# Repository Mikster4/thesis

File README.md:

# Thesis

Repo containing all files, design and photos created for the master thesis

# Links

Inverse kinematics: https://www.xarg.org/paper/inverse-kinematics-of-a-stewart-platform/

Simulation af en platform (i JS??): https://github.com/infusion/Stewart

Bibliotek til platform med servoer: https://github.com/Yeok-c/Stewart_Py

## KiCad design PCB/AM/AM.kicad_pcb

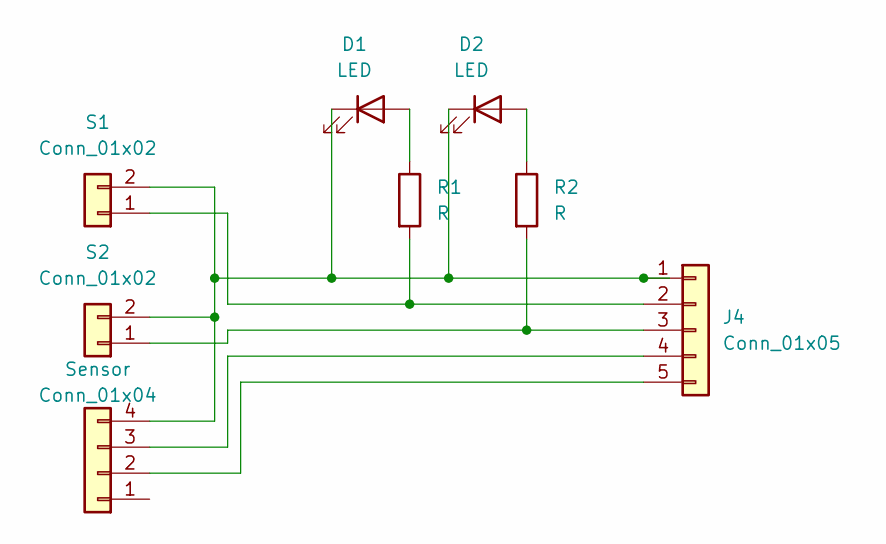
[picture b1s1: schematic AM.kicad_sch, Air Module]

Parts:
D1, D2: LED; LED_D5.0mm
J4: Conn_01x05; PinHeader_1x05_P2.54mm_Vertical
R1, R2: R; R_Axial_DIN0204_L3.6mm_D1.6mm_P7.62mm_Horizontal
S1, S2: Conn_01x02; PinHeader_1x02_P2.54mm_Vertical
Sensor: Conn_01x04; PinHeader_1x04_P2.54mm_Vertical

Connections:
unnamed: D1.1 (K), D2.1 (K), J4.1, S1.2, S2.2, Sensor.4
unnamed: D1.2 (A), R1.1
unnamed: D2.2 (A), R2.1
unnamed: J4.2, R1.2, S1.1
unnamed: J4.3, R2.2, S2.1
unnamed: J4.5, Sensor.2
unnamed: J4.4, Sensor.3

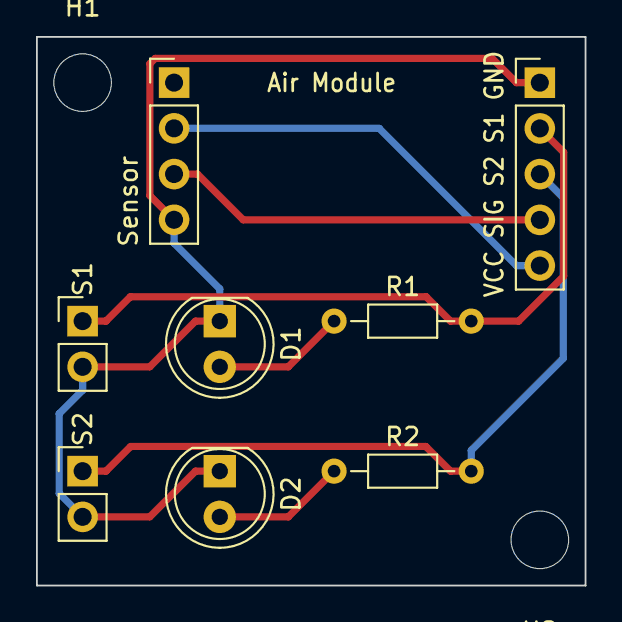
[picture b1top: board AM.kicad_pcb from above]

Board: 2 copper layers, 30.5 x 30.5 mm, 10 parts (0 on the bottom side), 7 nets.

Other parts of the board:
H1, H2: MountingHole_3.2mm_M3

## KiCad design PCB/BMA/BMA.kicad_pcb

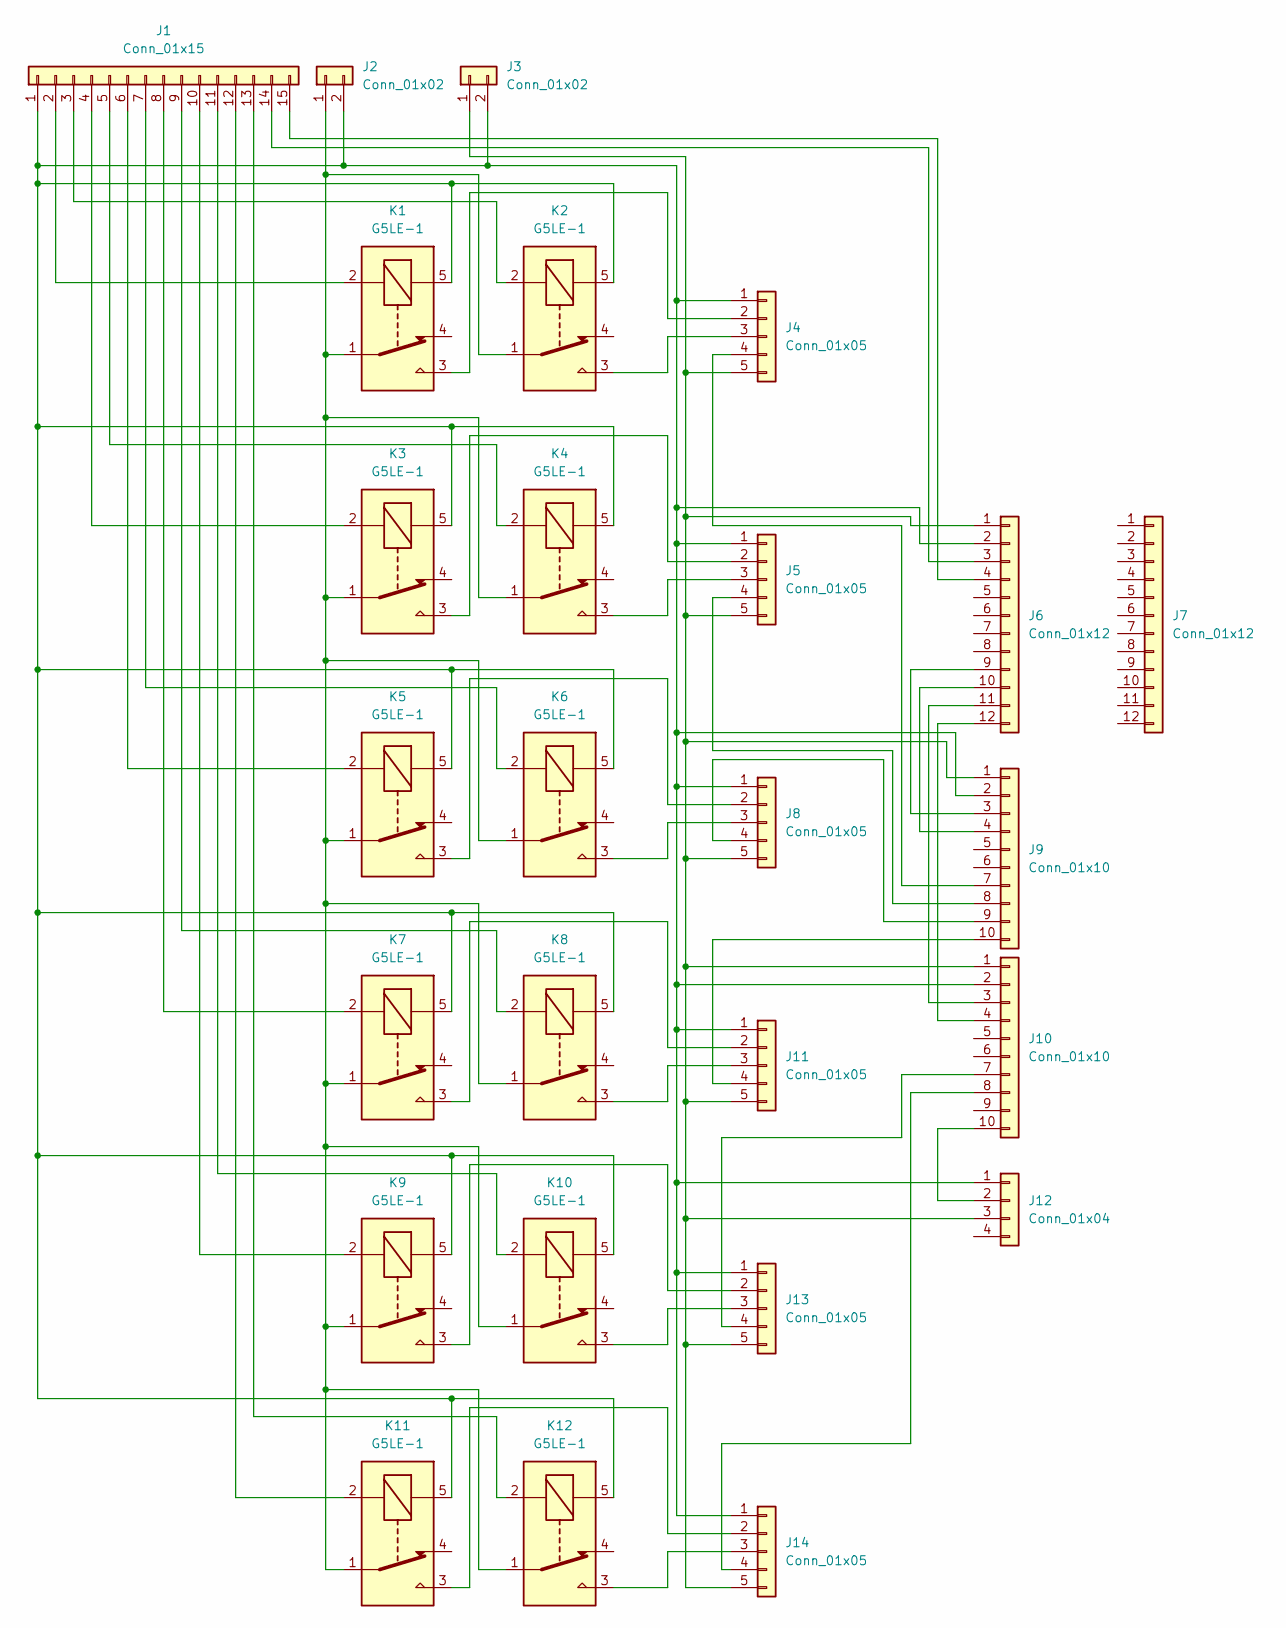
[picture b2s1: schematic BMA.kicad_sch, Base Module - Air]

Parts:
J1: Conn_01x15; PinHeader_1x15_P2.54mm_Vertical
J2, J3: Conn_01x02; PinHeader_1x02_P2.54mm_Vertical
J4, J5, J8, J11, J13, J14: Conn_01x05; PinHeader_1x05_P2.54mm_Vertical
J6, J7: Conn_01x12; PinHeader_1x12_P2.54mm_Vertical
J9, J10: Conn_01x10; PinHeader_1x10_P2.54mm_Vertical
J12: Conn_01x04; PinHeader_1x04_P2.54mm_Vertical
K1, K2, K3, K4, K5, K6, K7, K8, K9, K10, K11, K12: G5LE-1; Relay_SPDT_Omron-G5LE-1

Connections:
unnamed: J1.1, J2.2, J3.2, J4.1, J5.1, J6.2, J8.1, J9.2, J10.2, J11.1, J12.1, J13.1, J14.1, K1.5, K2.5, K3.5, K4.5, K5.5, K6.5, K7.5, K8.5, K9.5, K10.5, K11.5, K12.5
unnamed: J1.2, K1.2
unnamed: J1.3, K2.2
unnamed: J1.4, K3.2
unnamed: J1.5, K4.2
unnamed: J1.6, K5.2
unnamed: J1.7, K6.2
unnamed: J1.8, K7.2
unnamed: J1.9, K8.2
unnamed: J1.10, K9.2
unnamed: J1.11, K10.2
unnamed: J1.12, K11.2
unnamed: J1.13, K12.2
unnamed: J1.14, J6.3
unnamed: J1.15, J6.4
unnamed: J2.1, K1.1, K2.1, K3.1, K4.1, K5.1, K6.1, K7.1, K8.1, K9.1, K10.1, K11.1, K12.1
unnamed: J4.2, K1.3
unnamed: J4.3, K2.3
unnamed: J4.4, J9.7
unnamed: J5.2, K3.3
unnamed: J5.3, K4.3
unnamed: J5.4, J9.8
unnamed: J6.9, J9.3
unnamed: J6.10, J9.4
unnamed: J8.2, K5.3
unnamed: J8.3, K6.3
unnamed: J8.4, J9.9
unnamed: J3.1, J4.5, J5.5, J6.1, J8.5, J9.1, J10.1, J11.5, J12.3, J13.5, J14.5
unnamed: J6.11, J10.3
unnamed: J6.12, J10.4
unnamed: J10.7, J13.4
unnamed: J10.8, J14.4
unnamed: J10.10, J12.2
unnamed: J11.2, K7.3
unnamed: J11.3, K8.3
unnamed: J9.10, J11.4
unnamed: J13.2, K9.3
unnamed: J13.3, K10.3
unnamed: J14.2, K11.3
unnamed: J14.3, K12.3

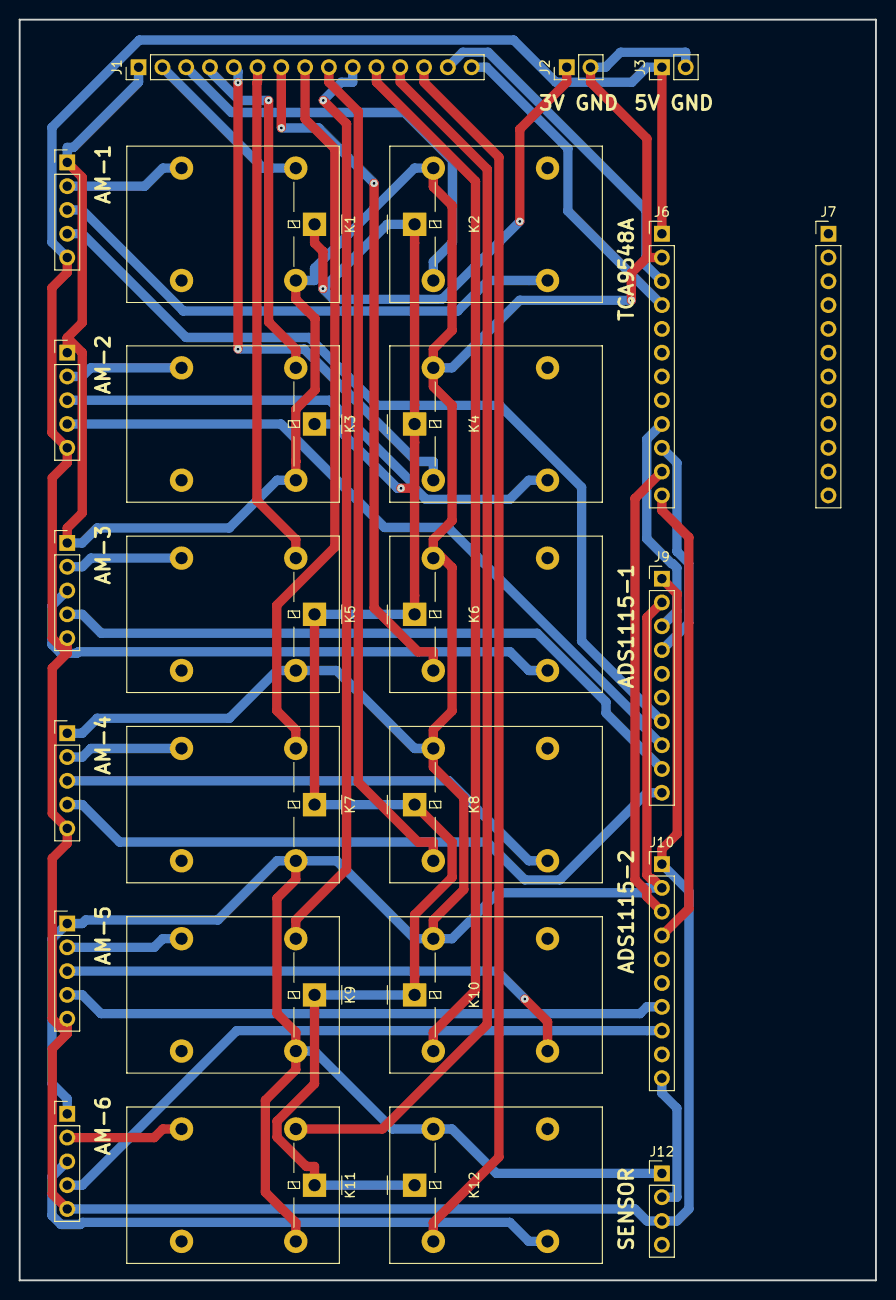
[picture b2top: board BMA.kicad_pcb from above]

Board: 2 copper layers, 91.4 x 134.6 mm, 26 parts (0 on the bottom side), 40 nets.

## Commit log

2023-01-03 Some progress
2023-01-05 POC 4
2023-01-05 Fixed drill size for vias
2023-01-15 POC 5
2023-01-18 Cleaning, schematics and POC 5
2023-01-24 More STLs
2023-01-24 Images
2023-01-24 Photos
2023-02-18 Renames
2023-02-23 Flere billedere
2023-03-06 Code has some functionality
2023-03-11 Analyze data
2023-03-11 Serial
2023-03-11 More data
2023-03-14 Platform leg lengths
2023-03-15 BM picture
